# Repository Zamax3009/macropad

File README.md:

# macropad
small macropad with 6 buttons and a knob.
I designed the pcb in kicad and the case in onshape: https://cad.onshape.com/documents/361361f4da3fd5bfe56361f3/w/ff9e29439e895af8a1cfd687/e/00a2e28cb5d51279b6564af9?renderMode=0&uiState=6a57934bb801166114ed1b02

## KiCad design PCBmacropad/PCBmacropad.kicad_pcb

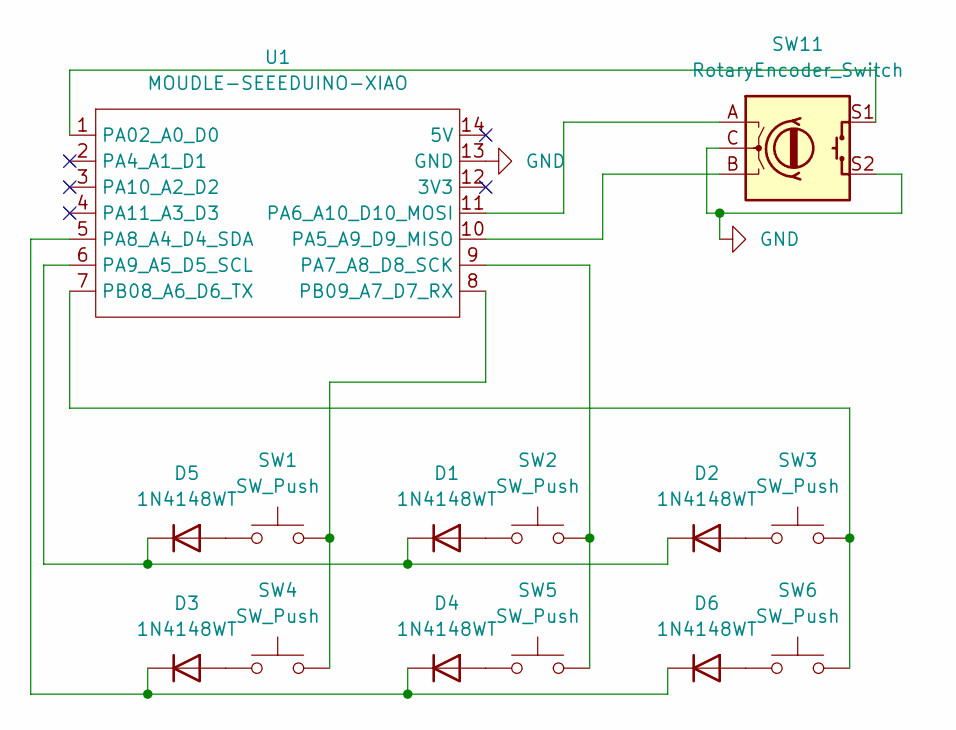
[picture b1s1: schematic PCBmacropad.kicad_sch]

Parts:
D1, D2, D3, D4, D5, D6: 1N4148WT; D_SOD-523
SW1, SW2, SW3, SW4, SW5, SW6: SW_Push; SW_Cherry_MX_1.00u_PCB
SW11: RotaryEncoder_Switch; RotaryEncoder_Alps_EC11E-Switch_Vertical_H20mm
U1: MOUDLE-SEEEDUINO-XIAO; XIAO-Generic-Hybrid-14P-2.54-21X17.8MM

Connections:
GND: SW11.C, SW11.S2, U1.13 (GND)
unnamed: D1.2 (A), SW2.1
unnamed: D1.1 (K), D2.1 (K), D5.1 (K), U1.6 (PA9_A5_D5_SCL)
unnamed: D2.2 (A), SW3.1
unnamed: D3.2 (A), SW4.1
unnamed: D3.1 (K), D4.1 (K), D6.1 (K), U1.5 (PA8_A4_D4_SDA)
unnamed: D4.2 (A), SW5.1
unnamed: D5.2 (A), SW1.1
unnamed: D6.2 (A), SW6.1
unnamed: SW11.S1, U1.1 (PA02_A0_D0)
unnamed: SW11.B, U1.10 (PA5_A9_D9_MISO)
unnamed: SW11.A, U1.11 (PA6_A10_D10_MOSI)
unnamed: SW2.2, SW5.2, U1.9 (PA7_A8_D8_SCK)
unnamed: SW3.2, SW6.2, U1.7 (PB08_A6_D6_TX)
unnamed: SW1.2, SW4.2, U1.8 (PB09_A7_D7_RX)

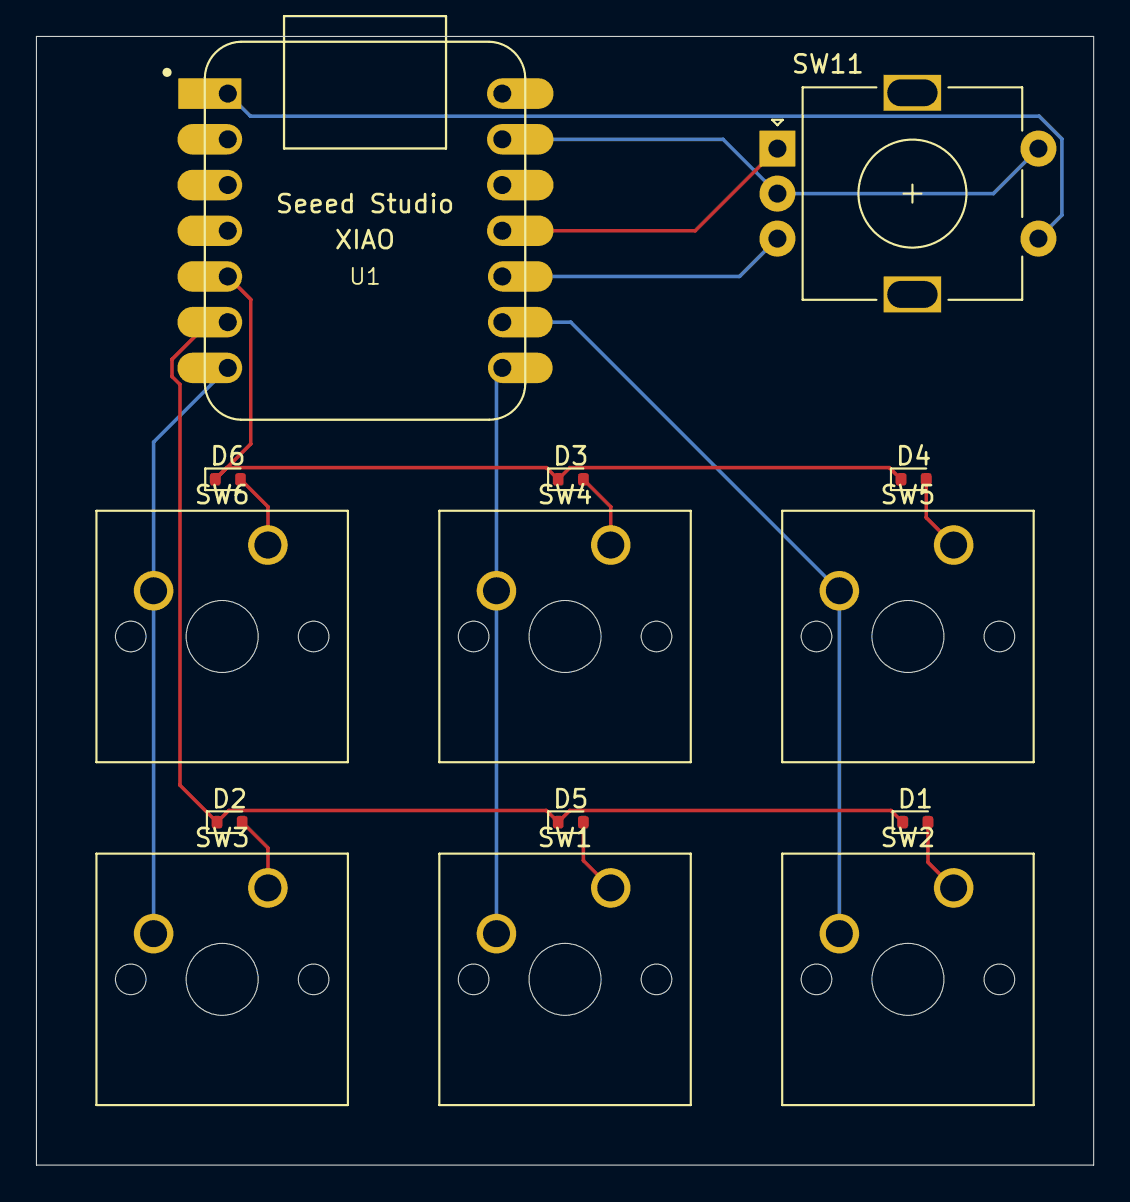
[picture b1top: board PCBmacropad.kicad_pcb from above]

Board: 2 copper layers, 58.7 x 62.7 mm, 14 parts (0 on the bottom side), 15 nets.
